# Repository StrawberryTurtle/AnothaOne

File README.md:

# AnothaOne

Only the worlds greatest one handed 8 key keyboard... supposedly according to me.

ZMK/QMK firmware for dedicated board in progress, but, a list of combos and an example keymap can be found in keymap.c to apply at free will.

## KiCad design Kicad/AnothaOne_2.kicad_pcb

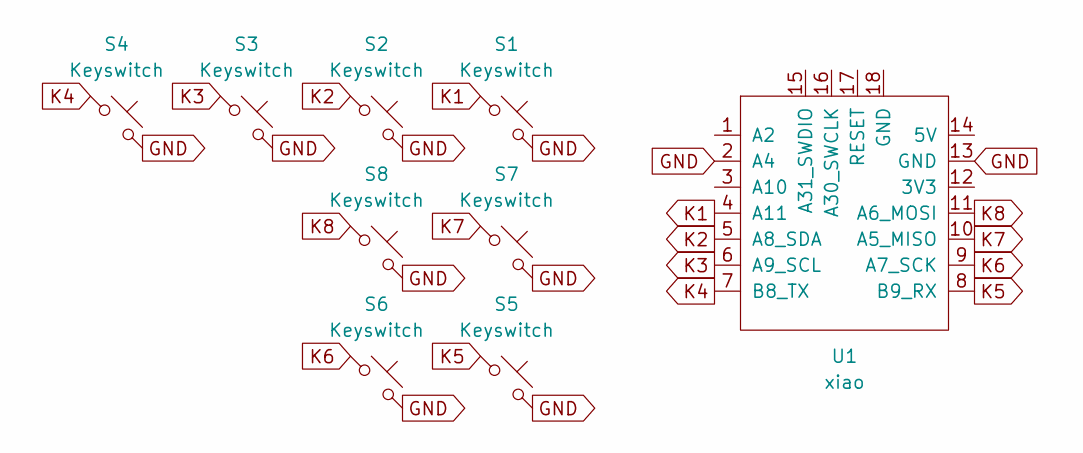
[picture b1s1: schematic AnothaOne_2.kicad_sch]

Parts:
S1, S2, S7, S8: Keyswitch; Choc_V1_1.00u
S3: Keyswitch; Choc_V1_2.00u
S4, S5, S6: Keyswitch; Choc_V1_1.50u
U1: xiao; XIAO-nRF52840-DIP

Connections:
GND: S1.2, S2.2, S3.2, S4.2, S5.2, S6.2, S7.2, S8.2, U1.2 (A4), U1.13 (GND)
K1: S1.1, U1.4 (A11)
K2: S2.1, U1.5 (A8_SDA)
K3: S3.1, U1.6 (A9_SCL)
K4: S4.1, U1.7 (B8_TX)
K5: S5.1, U1.8 (B9_RX)
K6: S6.1, U1.9 (A7_SCK)
K7: S7.1, U1.10 (A5_MISO)
K8: S8.1, U1.11 (A6_MOSI)

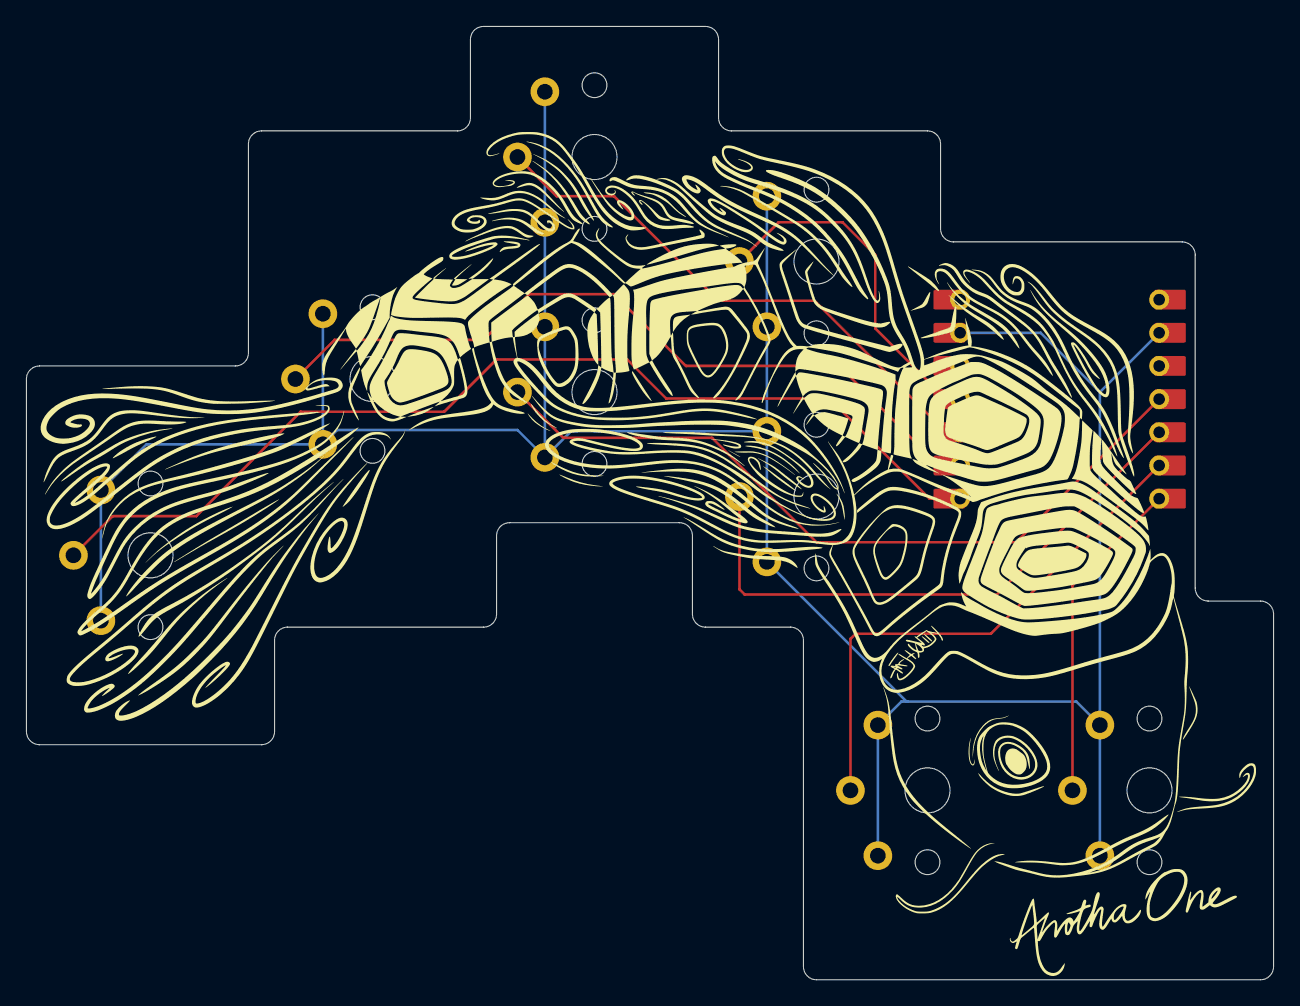
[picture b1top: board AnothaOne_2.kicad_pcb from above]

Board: 2 copper layers, 95.5 x 73.0 mm, 9 parts (0 on the bottom side), 9 nets.

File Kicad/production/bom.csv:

Designator,Footprint,Quantity,Value,LCSC Part #
"S1, S2, S7, S8",Choc_V1_1.00u,4,Keyswitch,
S3,Choc_V1_2.00u,1,Keyswitch,
"S4, S5, S6",Choc_V1_1.50u,3,Keyswitch,
U1,XIAO-nRF52840-DIP,1,xiao,

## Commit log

2025-05-08 Rename IMG_20250422_184333002.jpg to Top
2025-05-08 Rename IMG_20250421_195841053~2.jpg to PCB Art
